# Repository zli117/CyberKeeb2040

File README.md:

# CyberKeeb 2040
A mechnical keyboard and a cyberdeck. Powered by [PicoMK](https://github.com/zli117/PicoMK) for communication between RP2040 and Pi Zero. Watch the demo on YouTube 👇.

# Table of Contents

- [CyberKeeb 2040](#cyberkeeb-2040)
- [Table of Contents](#table-of-contents)
- [Build](#build)
  - [PCB](#pcb)
  - [Frame](#frame)
- [Photos](#photos)
  - [V2](#v2)
  - [V1](#v1)
- [Q\&A](#qa)
- [PCB Library Licenses](#pcb-library-licenses)

# Build

[**V2 parts list and build instructions**](Docs/BuildInstructions_V2.md)

[V1 parts list and build instructions](Docs/BuildInstructions_V1.md)

## PCB
Everything is in [PCB/MainBoard](PCB/MainBoard) dir. Designed with Kicad 7.0. Make sure `Perfect DOS VGA 437 Font` is intalled on Windows, or if you use Arch, install the [ttf-perfectdos](https://aur.archlinux.org/packages/ttf-perfectdos) package. [PCB/MainBoard/Gerber](PCB/MainBoard/Gerber) dir contains the Gerber files for three fab houses: [JLCPCB](PCB/MainBoard/Gerber/JLCPCB/), [PCBWay](PCB/MainBoard/Gerber/PCBWay/), and [OSHPark](PCB/MainBoard/Gerber/OSHPark/). For JLCPCB and PCBWay, **make sure to select the Castellated Holes option** (this will increase the price, but I found it necessary for good castellated holes).

## Frame
The frame has three acrylic plates and is held together with screws and standoffs.

 * [Frame/MainBoard/TopBar.dxf](Frame/MainBoard/TopBar.dxf): 3mm acrlyic
 * [Frame/MainBoard/Plate.dxf](Frame/MainBoard/Plate.dxf): 1.5mm acrlyic
 * [Frame/MainBoard/Bottom.dxf](Frame/MainBoard/Bottom.dxf): 3mm acrlyic

# Photos

## V2

## V1

# Q&A

Special thanks to [icon-oclast](https://github.com/icon-oclast) for [asking](https://github.com/zli117/CyberKeeb2040/issues/2) these great questions.

> What are the dip switches used for? Is there a recommended default setting for these?

The 4 positions are for each line of the SPI connection between the pi pico and pi zero. This allows cutting the connections between pi pico and pi zero without cutting the power connections. I initially designed it for the (paranoid) scenario where I can't kill the pi zero, but doesn't want it to do autotype or receiving the key strokes, but I found such scenario increasing unlikely. So, if you don't want to solder the DIP switches, feel free to just short the corresponding pins.

> Presumably the switch/jumper labeled "pi power" controls pass-through power from the Pico to the Zero?

Yes.

> Is there a minimum USB current needed when powering both boards

I don't have the empirical measurements, but here's the estimate:
Pico: <20mA. Data source: https://mjoldfield.com/atelier/2021/11/pico-power.html
SSD1306: <7mA. Data source: https://hsel.co.uk/2018/12/04/ssd1306-power-consumption/
Pi Zero W: <400mA under stress. Data source: https://www.tomshardware.com/reviews/raspberry-pi-zero-2-w-review
Pi Zero 2 W: <600mA under stress.

So let's say it's 700mA if you want to stress the pi zero. I did run the stressberry on pi zero 2 w, with the display hat, and a wireless mouse receiver. The board is connected to the USB3.0 port and there's no under voltage warning, and no visible heat up on the cable or the connectors. However, due to differences on the motherboards, YMMY. I currently don't have a USB power meter to measure the actual current drawn.

> Is there a maximum safe current to pass-through (when using the optional display hat for example)?

The trace between pico and pi zero has width of 1mm, and length around 300mm. Assuming you're using 1oz copper thickness, it should result in a maximum current of 1.2 A for temperature rise of 10 degree C.

> Is it safe to power the zero independently by setting the pi power switch/jumper to off?

Yes.

> What about the two connectors at the bottom of the board, either 4-pin jst sockets as in the build instructions, or possibly 5-pin headers on some revisions of the pcb, how are they intended to be used?

They are for my future plans :) Essentially, they expose three buttons from the key scan matrix, and pin 26 and 27. Pin 26 and 27 are analog input pins and I2C 1. I'm planning to create a plugin module for the joystick mouse pad similar to the one I have on the Pico-Keyboard, and an I2C expansion board for more modules like a num pad. 

> What cool things can we do if we include the optional 90 degree pin header(s)?

The pin header under the small screen has been removed, because I figured it'll be difficult to use it for anything without creating a giant mess in the firmware. The other header exposes the addressable LEDs. Only WS2812 is supported and tested because it's used in the Pico-Keyboard. However, you might be able to use for other things as it's essentially a GPIO pin with ground and 5V, and a 330 ohm resister on the GPIO pin.

# PCB Library Licenses

 * Pico symbol, footprint from https://github.com/ncarandini/KiCad-RP-Pico under CC-BY-SA 4.0. 3D model for Pico is obtained from Raspberry Pi Foundation.
 * Pi Zero symbol, footprint and 3D model are from [SnapEDA](https://www.snapeda.com/parts/ADA3708/Adafruit%20Industries%20LLC/view-part/) under [CC BY-SA 4.0](https://support.snapeda.com/en/articles/2957814-what-is-the-license-for-symbols-and-footprints)
 * Key switch footprints and 3D models are from https://github.com/kiswitch/kiswitch
 * PJ320A symbol, footprint are from [Keebio-Parts.pretty](https://github.com/keebio/Keebio-Parts.pretty/blob/master/TRRS-PJ-320A.kicad_mod) under MIT License.
 * Other symbols are from KiCad library which is under CC-BY-SA 4.0 license. 

This work is licensed under a
[Creative Commons Attribution-ShareAlike 4.0 International License][cc-by-sa].

[![CC BY-SA 4.0][cc-by-sa-image]][cc-by-sa]

[cc-by-sa]: http://creativecommons.org/licenses/by-sa/4.0/
[cc-by-sa-image]: https://licensebuttons.net/l/by-sa/4.0/88x31.png
[cc-by-sa-shield]: https://img.shields.io/badge/License-CC%20BY--SA%204.0-lightgrey.svg

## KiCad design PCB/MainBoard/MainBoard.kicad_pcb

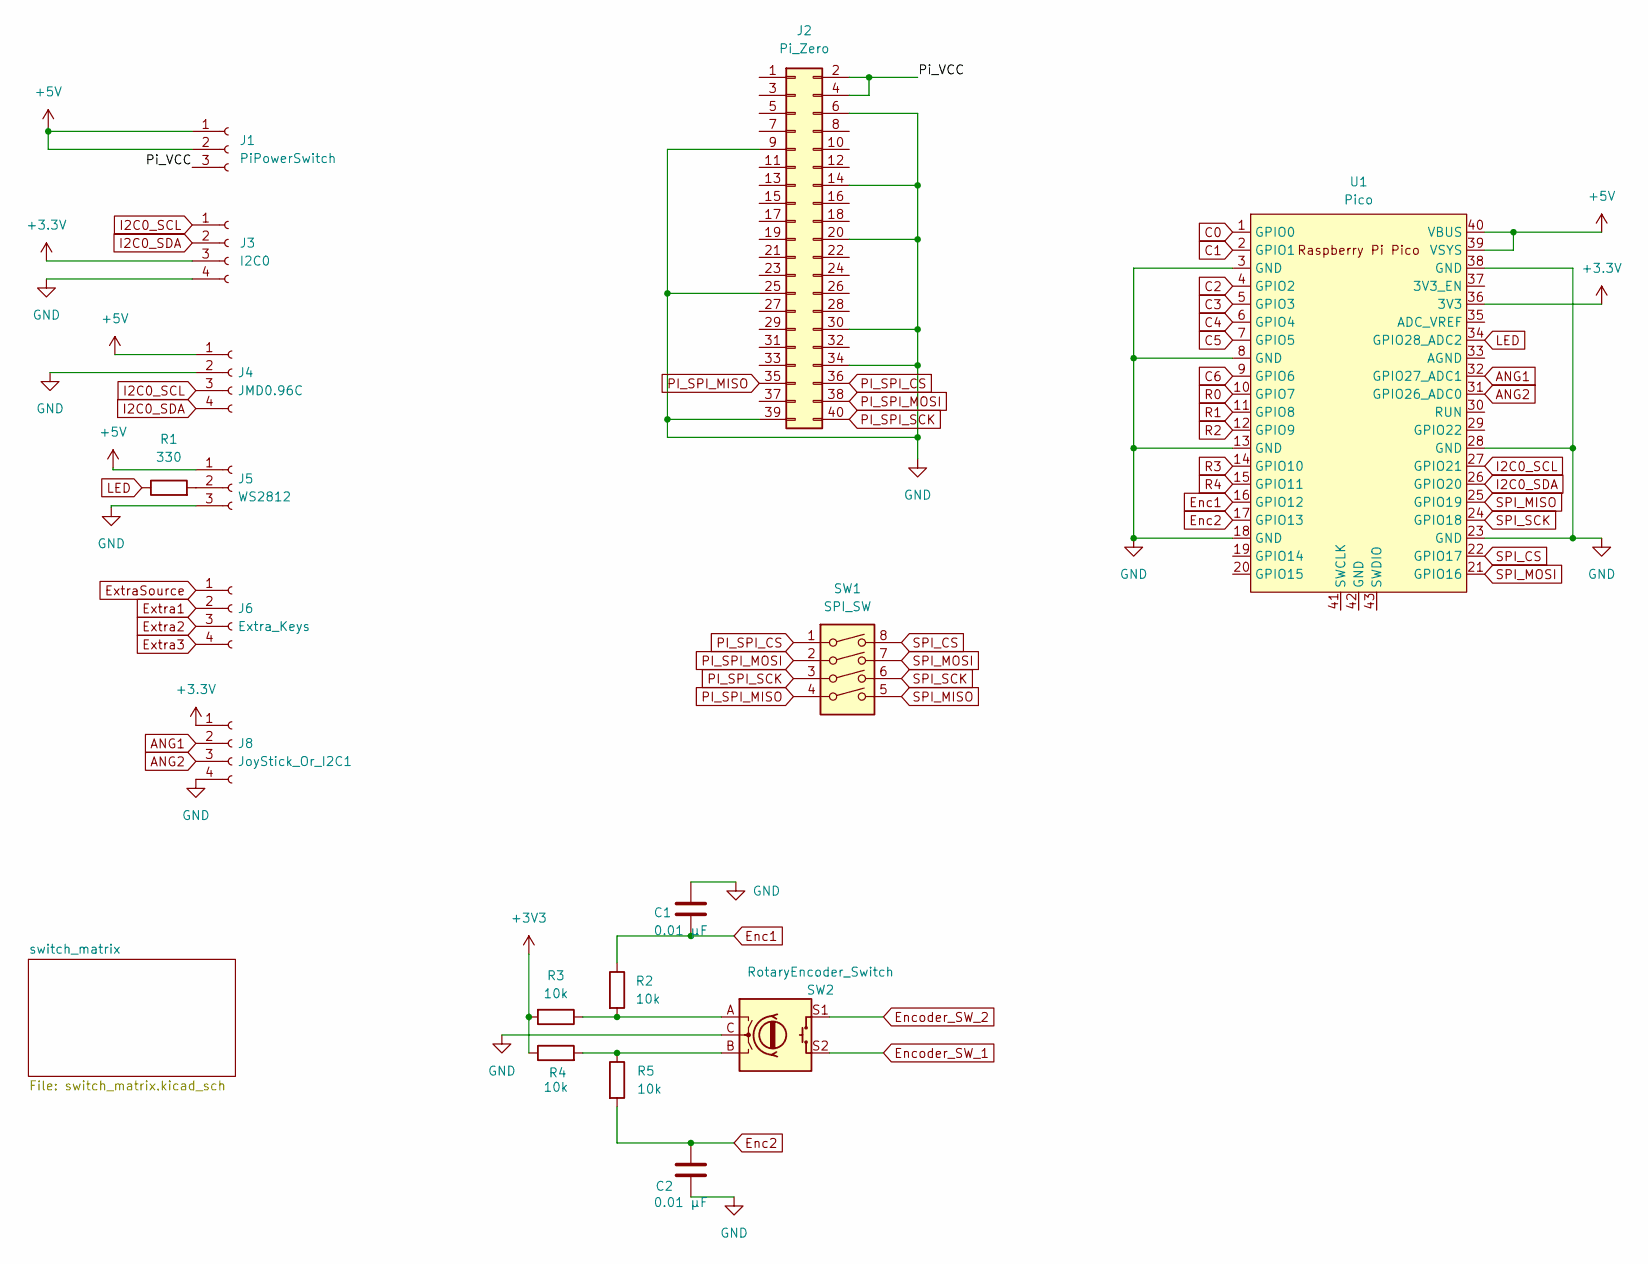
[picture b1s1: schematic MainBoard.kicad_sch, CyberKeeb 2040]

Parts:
C1, C2: 0.01 μF; C_1206_3216Metric_Pad1.33x1.80mm_HandSolder
J1: PiPowerSwitch; PinHeader_1x03_P2.54mm_Vertical
J2: Pi_Zero; Raspberry_Pi_Zero_Socketed_THT_MountingHoles_Castellated
J3: I2C0; PinHeader_1x04_P2.54mm_Horizontal
J4: JMD0.96C
J5: WS2812; PinHeader_1x03_P2.54mm_Horizontal
J6: Extra_Keys; JST_PH_S4B-PH-K_1x04_P2.00mm_Horizontal
J8: JoyStick_Or_I2C1; JST_PH_S4B-PH-K_1x04_P2.00mm_Horizontal
R1: 330; R_Axial_DIN0207_L6.3mm_D2.5mm_P10.16mm_Horizontal
R2, R3, R4, R5: 10k; R_Axial_DIN0207_L6.3mm_D2.5mm_P10.16mm_Horizontal
SW1: SPI_SW; SW_DIP_SPSTx04_Slide_6.7x11.72mm_W7.62mm_P2.54mm_LowProfile
SW2: RotaryEncoder_Switch; RotaryEncoder_Alps_EC11E-Switch_Vertical_H20mm_CircularMoun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
U1: Pico; RPi_Pico_SMD_TH

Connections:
+5V: J1.1, J1.2, J4.1, J5.1, U1.39 (VSYS), U1.40 (VBUS)
/Pi_VCC: J1.3, J2.2, J2.4
ANG1: J8.2, U1.32 (GPIO27_ADC1)
ANG2: J8.3, U1.31 (GPIO26_ADC0)
C0: U1.1 (GPIO0); also elsewhere on the board
C1: U1.2 (GPIO1); also elsewhere on the board
C2: U1.4 (GPIO2); also elsewhere on the board
C3: U1.5 (GPIO3); also elsewhere on the board
C4: U1.6 (GPIO4); also elsewhere on the board
C5: U1.7 (GPIO5); also elsewhere on the board
C6: U1.9 (GPIO6); also elsewhere on the board
Enc1: C1.2, R2.1, U1.16 (GPIO12)
Enc2: C2.1, R5.2, U1.17 (GPIO13)
Encoder_SW_1: SW2.S2; also elsewhere on the board
Encoder_SW_2: SW2.S1; also elsewhere on the board
Extra1: J6.2; also elsewhere on the board
Extra2: J6.3; also elsewhere on the board
Extra3: J6.4; also elsewhere on the board
ExtraSource: J6.1; also elsewhere on the board
GND: C1.1, C2.2, J2.6, J2.9, J2.14, J2.20, J2.25, J2.30, J2.34, J2.39, J3.4, J4.2, J5.3, J8.4, SW2.C, U1.3 (GND), U1.8 (GND), U1.13 (GND), U1.18 (GND), U1.23 (GND), U1.28 (GND), U1.38 (GND)
I2C0_SCL: J3.1, J4.3, U1.27 (GPIO21)
I2C0_SDA: J3.2, J4.4, U1.26 (GPIO20)
LED: R1.1, U1.34 (GPIO28_ADC2)
unnamed: J5.2, R1.2
unnamed: R2.2, R3.1, SW2.A
unnamed: R4.2, R5.1, SW2.B
PI_SPI_CS: J2.36, SW1.1
PI_SPI_MISO: J2.35, SW1.4
PI_SPI_MOSI: J2.38, SW1.2
PI_SPI_SCK: J2.40, SW1.3
R0: U1.10 (GPIO7); also elsewhere on the board
R1: U1.11 (GPIO8); also elsewhere on the board
R2: U1.12 (GPIO9); also elsewhere on the board
R3: U1.14 (GPIO10); also elsewhere on the board
R4: U1.15 (GPIO11); also elsewhere on the board
SPI_CS: SW1.8, U1.22 (GPIO17)
SPI_MISO: SW1.5, U1.25 (GPIO19)
SPI_MOSI: SW1.7, U1.21 (GPIO16)
SPI_SCK: SW1.6, U1.24 (GPIO18)

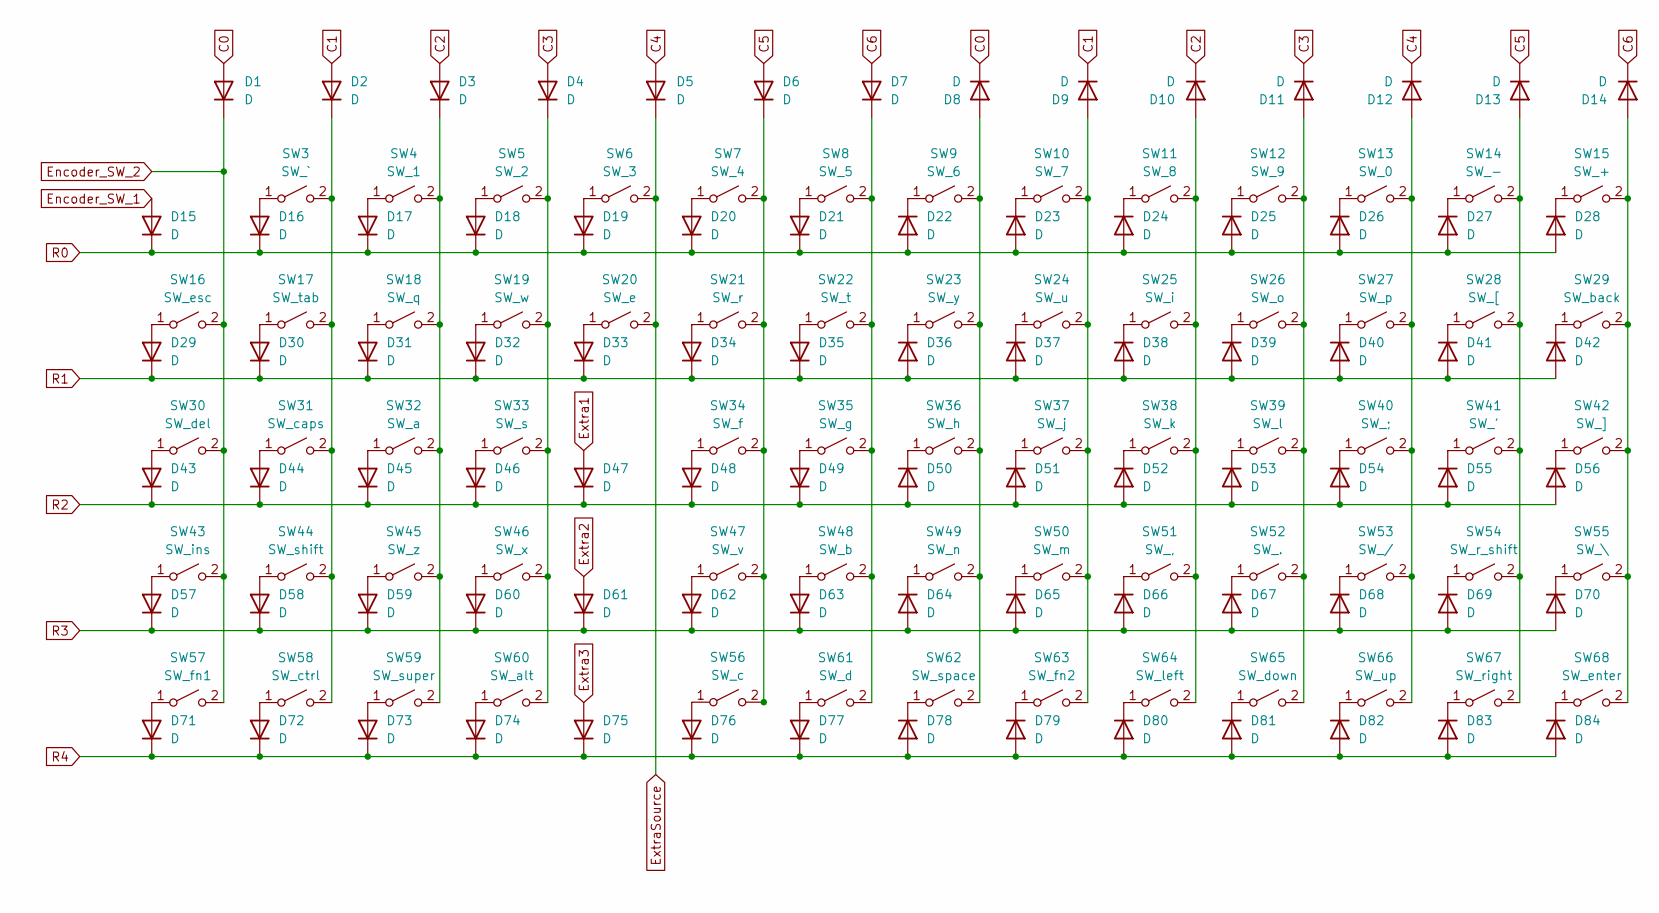
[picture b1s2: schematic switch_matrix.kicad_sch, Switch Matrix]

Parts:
D1, D2, D3, D4, D5, D6, D7, D8, D9, D10, D11, D12, D13, D14, D15, D16, D17, D18, D19, D20, D21, D22, D23, D24, D25, D26, D27, D28, D29, D30, D31, D32, D33, D34, D35, D36, D37, D38, D39, D40, D41, D42, D43, D44, D45, D46, D47, D48, D49, D50, D51, D52, D53, D54, D55, D56, D57, D58, D59, D60, D61, D62, D63, D64, D65, D66, D67, D68, D69, D70, D71, D72, D73, D74, D75, D76, D77, D78, D79, D80, D81, D82, D83, D84: D; D_DO-35_SOD27_P7.62mm_Horizontal
SW3: SW_`; SW_Hotswap_Kailh_MX_1.00u
SW4: SW_1; SW_Hotswap_Kailh_MX_1.00u
SW5: SW_2; SW_Hotswap_Kailh_MX_1.00u
SW6: SW_3; SW_Hotswap_Kailh_MX_1.00u
SW7: SW_4; SW_Hotswap_Kailh_MX_1.00u
SW8: SW_5; SW_Hotswap_Kailh_MX_1.00u
SW9: SW_6; SW_Hotswap_Kailh_MX_1.00u
SW10: SW_7; SW_Hotswap_Kailh_MX_1.00u
SW11: SW_8; SW_Hotswap_Kailh_MX_1.00u
SW12: SW_9; SW_Hotswap_Kailh_MX_1.00u
SW13: SW_0; SW_Hotswap_Kailh_MX_1.00u
SW14: SW_-; SW_Hotswap_Kailh_MX_1.00u
SW15: SW_+; SW_Hotswap_Kailh_MX_1.00u
SW16: SW_esc; SW_Hotswap_Kailh_MX_1.00u
SW17: SW_tab; SW_Hotswap_Kailh_MX_1.50u
SW18: SW_q; SW_Hotswap_Kailh_MX_1.00u
SW19: SW_w; SW_Hotswap_Kailh_MX_1.00u
SW20: SW_e; SW_Hotswap_Kailh_MX_1.00u
SW21: SW_r; SW_Hotswap_Kailh_MX_1.00u
SW22: SW_t; SW_Hotswap_Kailh_MX_1.00u
SW23: SW_y; SW_Hotswap_Kailh_MX_1.00u
SW24: SW_u; SW_Hotswap_Kailh_MX_1.00u
SW25: SW_i; SW_Hotswap_Kailh_MX_1.00u
SW26: SW_o; SW_Hotswap_Kailh_MX_1.00u
SW27: SW_p; SW_Hotswap_Kailh_MX_1.00u
SW28: SW_[; SW_Hotswap_Kailh_MX_1.00u
SW29: SW_back; SW_Hotswap_Kailh_MX_2.00u
SW30: SW_del; SW_Hotswap_Kailh_MX_1.00u
SW31: SW_caps; SW_Hotswap_Kailh_MX_1.75u
SW32: SW_a; SW_Hotswap_Kailh_MX_1.00u
SW33: SW_s; SW_Hotswap_Kailh_MX_1.00u
SW34: SW_f; SW_Hotswap_Kailh_MX_1.00u
SW35: SW_g; SW_Hotswap_Kailh_MX_1.00u
SW36: SW_h; SW_Hotswap_Kailh_MX_1.00u
SW37: SW_j; SW_Hotswap_Kailh_MX_1.00u
SW38: SW_k; SW_Hotswap_Kailh_MX_1.00u
SW39: SW_l; SW_Hotswap_Kailh_MX_1.00u
SW40: SW_;; SW_Hotswap_Kailh_MX_1.00u
SW41: SW_'; SW_Hotswap_Kailh_MX_1.00u
SW42: SW_]; SW_Hotswap_Kailh_MX_1.00u
SW43: SW_ins; SW_Hotswap_Kailh_MX_1.00u
SW44: SW_shift; SW_Hotswap_Kailh_MX_2.25u
SW45: SW_z; SW_Hotswap_Kailh_MX_1.00u
SW46: SW_x; SW_Hotswap_Kailh_MX_1.00u
SW47: SW_v; SW_Hotswap_Kailh_MX_1.00u
SW48: SW_b; SW_Hotswap_Kailh_MX_1.00u
SW49: SW_n; SW_Hotswap_Kailh_MX_1.00u
SW50: SW_m; SW_Hotswap_Kailh_MX_1.00u
SW51: SW_,; SW_Hotswap_Kailh_MX_1.00u
SW52: SW_.; SW_Hotswap_Kailh_MX_1.00u
SW53: SW_/; SW_Hotswap_Kailh_MX_1.00u
SW54: SW_r_shift; SW_Hotswap_Kailh_MX_2.75u
SW55: SW_\; SW_Hotswap_Kailh_MX_1.50u
SW56: SW_c; SW_Hotswap_Kailh_MX_1.00u
SW57: SW_fn1; SW_Hotswap_Kailh_MX_1.00u
SW58: SW_ctrl; SW_Hotswap_Kailh_MX_1.25u
SW59: SW_super; SW_Hotswap_Kailh_MX_1.25u
SW60: SW_alt; SW_Hotswap_Kailh_MX_1.25u
SW61: SW_d; SW_Hotswap_Kailh_MX_1.00u
SW62: SW_space; SW_Hotswap_Kailh_MX_6.25u
SW63: SW_fn2; SW_Hotswap_Kailh_MX_1.00u
SW64: SW_left; SW_Hotswap_Kailh_MX_1.00u
SW65: SW_down; SW_Hotswap_Kailh_MX_1.00u
SW66: SW_up; SW_Hotswap_Kailh_MX_1.00u
SW67: SW_right; SW_Hotswap_Kailh_MX_1.00u
SW68: SW_enter; SW_Hotswap_Kailh_MX_2.25u

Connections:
C0: D1.2 (A), D8.1 (K); also elsewhere on the board
C1: D2.2 (A), D9.1 (K); also elsewhere on the board
C2: D3.2 (A), D10.1 (K); also elsewhere on the board
C3: D4.2 (A), D11.1 (K); also elsewhere on the board
C4: D5.2 (A), D12.1 (K); also elsewhere on the board
C5: D6.2 (A), D13.1 (K); also elsewhere on the board
C6: D7.2 (A), D14.1 (K); also elsewhere on the board
Encoder_SW_1: D15.2 (A); also elsewhere on the board
Encoder_SW_2: D1.1 (K), SW16.2 (B), SW30.2 (B), SW43.2 (B), SW57.2 (B); also elsewhere on the board
Extra1: D47.2 (A); also elsewhere on the board
Extra2: D61.2 (A); also elsewhere on the board
Extra3: D75.2 (A); also elsewhere on the board
ExtraSource: D5.1 (K), SW6.2 (B), SW20.2 (B); also elsewhere on the board
unnamed: D2.1 (K), SW3.2 (B), SW17.2 (B), SW31.2 (B), SW44.2 (B), SW58.2 (B)
unnamed: D3.1 (K), SW4.2 (B), SW18.2 (B), SW32.2 (B), SW45.2 (B), SW59.2 (B)
unnamed: D4.1 (K), SW5.2 (B), SW19.2 (B), SW33.2 (B), SW46.2 (B), SW60.2 (B)
unnamed: D6.1 (K), SW7.2 (B), SW21.2 (B), SW34.2 (B), SW47.2 (B), SW56.2 (B)
unnamed: D7.1 (K), SW8.2 (B), SW22.2 (B), SW35.2 (B), SW48.2 (B), SW61.2 (B)
unnamed: D8.2 (A), SW9.2 (B), SW23.2 (B), SW36.2 (B), SW49.2 (B), SW62.2 (B)
unnamed: D9.2 (A), SW10.2 (B), SW24.2 (B), SW37.2 (B), SW50.2 (B), SW63.2 (B)
unnamed: D10.2 (A), SW11.2 (B), SW25.2 (B), SW38.2 (B), SW51.2 (B), SW64.2 (B)
unnamed: D11.2 (A), SW12.2 (B), SW26.2 (B), SW39.2 (B), SW52.2 (B), SW65.2 (B)
unnamed: D12.2 (A), SW13.2 (B), SW27.2 (B), SW40.2 (B), SW53.2 (B), SW66.2 (B)
unnamed: D13.2 (A), SW14.2 (B), SW28.2 (B), SW41.2 (B), SW54.2 (B), SW67.2 (B)
unnamed: D14.2 (A), SW15.2 (B), SW29.2 (B), SW42.2 (B), SW55.2 (B), SW68.2 (B)
unnamed: D16.2 (A), SW3.1 (A)
unnamed: D17.2 (A), SW4.1 (A)
unnamed: D18.2 (A), SW5.1 (A)
unnamed: D19.2 (A), SW6.1 (A)
unnamed: D20.2 (A), SW7.1 (A)
unnamed: D21.2 (A), SW8.1 (A)
unnamed: D22.1 (K), SW9.1 (A)
unnamed: D23.1 (K), SW10.1 (A)
unnamed: D24.1 (K), SW11.1 (A)
unnamed: D25.1 (K), SW12.1 (A)
unnamed: D26.1 (K), SW13.1 (A)
unnamed: D27.1 (K), SW14.1 (A)
unnamed: D28.1 (K), SW15.1 (A)
unnamed: D29.2 (A), SW16.1 (A)
unnamed: D30.2 (A), SW17.1 (A)
unnamed: D31.2 (A), SW18.1 (A)
unnamed: D32.2 (A), SW19.1 (A)
unnamed: D33.2 (A), SW20.1 (A)
unnamed: D34.2 (A), SW21.1 (A)
unnamed: D35.2 (A), SW22.1 (A)
unnamed: D36.1 (K), SW23.1 (A)
unnamed: D37.1 (K), SW24.1 (A)
unnamed: D38.1 (K), SW25.1 (A)
unnamed: D39.1 (K), SW26.1 (A)
unnamed: D40.1 (K), SW27.1 (A)
unnamed: D41.1 (K), SW28.1 (A)
unnamed: D42.1 (K), SW29.1 (A)
unnamed: D43.2 (A), SW30.1 (A)
unnamed: D44.2 (A), SW31.1 (A)
unnamed: D45.2 (A), SW32.1 (A)
unnamed: D46.2 (A), SW33.1 (A)
unnamed: D48.2 (A), SW34.1 (A)
unnamed: D49.2 (A), SW35.1 (A)
unnamed: D50.1 (K), SW36.1 (A)
unnamed: D51.1 (K), SW37.1 (A)
unnamed: D52.1 (K), SW38.1 (A)
unnamed: D53.1 (K), SW39.1 (A)
unnamed: D54.1 (K), SW40.1 (A)
unnamed: D55.1 (K), SW41.1 (A)
unnamed: D56.1 (K), SW42.1 (A)
unnamed: D57.2 (A), SW43.1 (A)
unnamed: D58.2 (A), SW44.1 (A)
unnamed: D59.2 (A), SW45.1 (A)
unnamed: D60.2 (A), SW46.1 (A)
unnamed: D62.2 (A), SW47.1 (A)
unnamed: D63.2 (A), SW48.1 (A)
unnamed: D64.1 (K), SW49.1 (A)
unnamed: D65.1 (K), SW50.1 (A)
unnamed: D66.1 (K), SW51.1 (A)
unnamed: D67.1 (K), SW52.1 (A)
unnamed: D68.1 (K), SW53.1 (A)
unnamed: D69.1 (K), SW54.1 (A)
unnamed: D70.1 (K), SW55.1 (A)
unnamed: D71.2 (A), SW57.1 (A)
unnamed: D72.2 (A), SW58.1 (A)
unnamed: D73.2 (A), SW59.1 (A)
unnamed: D74.2 (A), SW60.1 (A)
unnamed: D77.2 (A), SW61.1 (A)
unnamed: D78.1 (K), SW62.1 (A)
unnamed: D79.1 (K), SW63.1 (A)
unnamed: D80.1 (K), SW64.1 (A)
unnamed: D81.1 (K), SW65.1 (A)
unnamed: D82.1 (K), SW66.1 (A)
unnamed: D83.1 (K), SW67.1 (A)
unnamed: D84.1 (K), SW68.1 (A)
R0: D15.1 (K), D16.1 (K), D17.1 (K), D18.1 (K), D19.1 (K), D20.1 (K), D21.1 (K), D22.2 (A), D23.2 (A), D24.2 (A), D25.2 (A), D26.2 (A), D27.2 (A), D28.2 (A); also elsewhere on the board
R1: D29.1 (K), D30.1 (K), D31.1 (K), D32.1 (K), D33.1 (K), D34.1 (K), D35.1 (K), D36.2 (A), D37.2 (A), D38.2 (A), D39.2 (A), D40.2 (A), D41.2 (A), D42.2 (A); also elsewhere on the board
R2: D43.1 (K), D44.1 (K), D45.1 (K), D46.1 (K), D47.1 (K), D48.1 (K), D49.1 (K), D50.2 (A), D51.2 (A), D52.2 (A), D53.2 (A), D54.2 (A), D55.2 (A), D56.2 (A); also elsewhere on the board
R3: D57.1 (K), D58.1 (K), D59.1 (K), D60.1 (K), D61.1 (K), D62.1 (K), D63.1 (K), D64.2 (A), D65.2 (A), D66.2 (A), D67.2 (A), D68.2 (A), D69.2 (A), D70.2 (A); also elsewhere on the board
R4: D71.1 (K), D72.1 (K), D73.1 (K), D74.1 (K), D75.1 (K), D76.1 (K), D77.1 (K), D78.2 (A), D79.2 (A), D80.2 (A), D81.2 (A), D82.2 (A), D83.2 (A), D84.2 (A); also elsewhere on the board

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
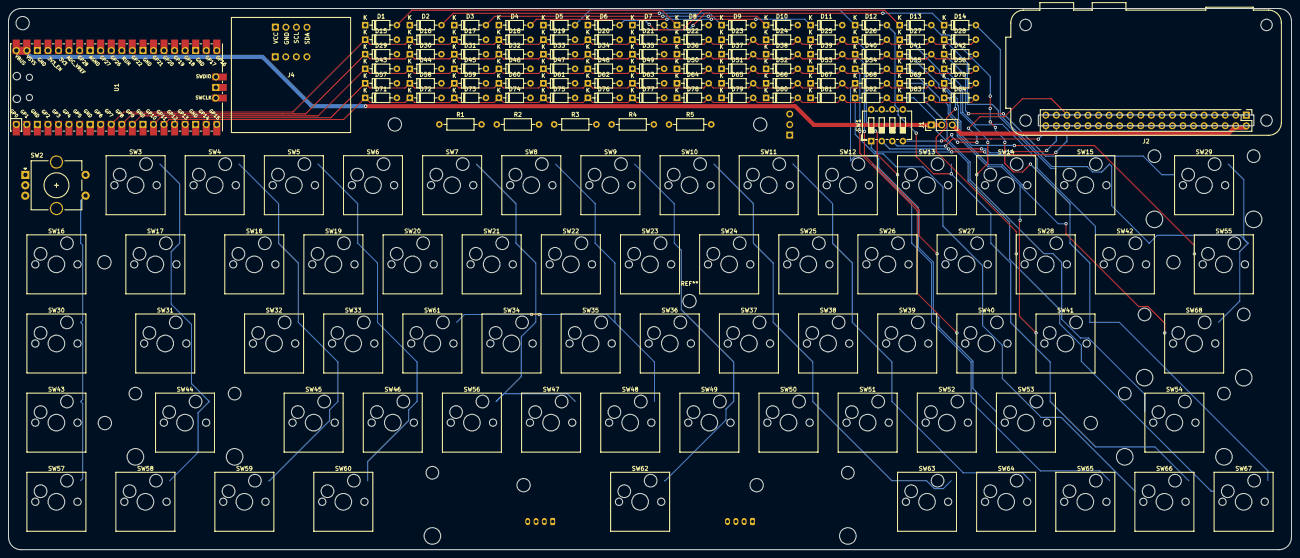
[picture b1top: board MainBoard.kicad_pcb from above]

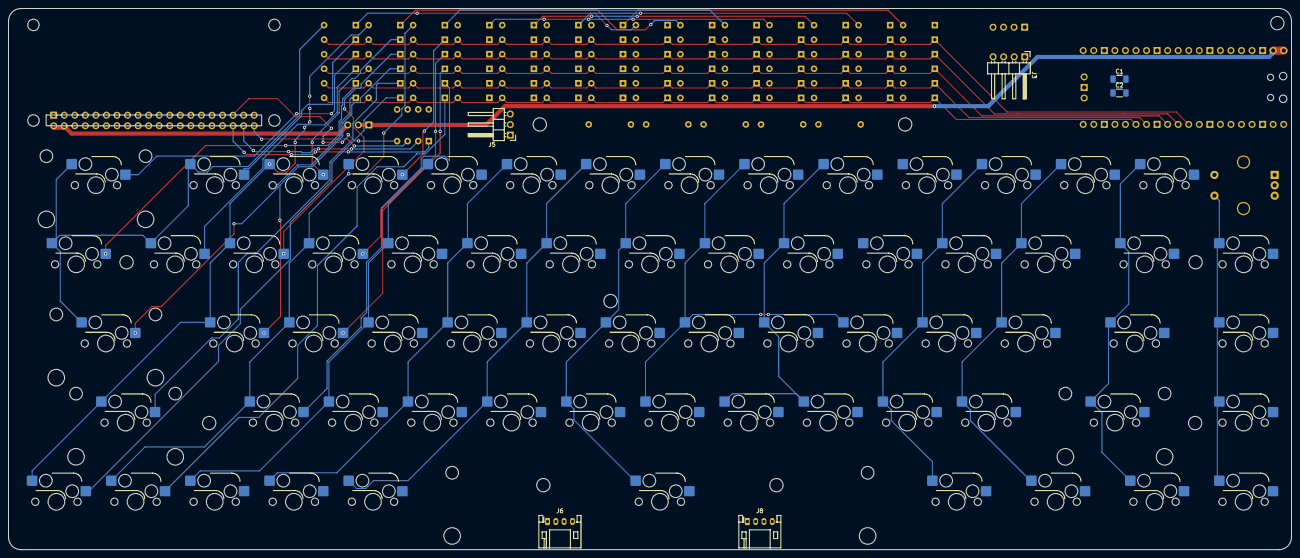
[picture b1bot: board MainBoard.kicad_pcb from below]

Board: 2 copper layers, 308.8 x 130.2 mm, 167 parts (6 on the bottom side), 117 nets.

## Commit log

2023-06-10 Added diodes for the duplex layout
2023-06-11 Updated 3d model
2023-06-11 Tentative layout
2023-06-11 Layout settled
2023-06-11 Updated layout to add mounting holes
2023-06-11 Crazy wiring
2023-06-12 Whatever
2023-06-14 Updated PCB
2023-06-14 Added gerber
2023-06-15 Added silkscreen label
2023-06-15 Updated github url
2023-06-18 Updated pcb a bit
2023-06-18 Custom diode footprint with proper silkscreen
2023-06-18 Fixed solder mask around the mounting hole for pi
2023-06-23 Added pcb step file
2023-06-24 Fixed 3d model for pi zero
2023-07-02 Updated 3d model for zero
2023-07-02 Added frame stl and dxf files
2023-07-03 Changed self tapping diameter
2023-07-03 Updated tapping hole diameter
2023-07-04 Fixed bottom plate hole
2023-07-08 Fixed the spacers, and added a thumb rest
2023-07-21 Updated bottom dxf
2023-08-19 Updated bottom spacer
2023-08-19 Updated plate dxf to have a rounded corner
2023-08-19 Use switch instead of jumper
2023-08-20 Added f3d file
2023-08-20 Create LICENSE
2023-08-20 Added instruction to install the driver
2023-08-20 Added table of contents
2023-09-04 Updated the bottom connector, and replotted the files
2023-09-04 Fixed pick and place center for switch footprint
2023-09-04 Forgot to uncomment something
2023-09-04 Fixed silkscreen for the diodes
2023-09-04 Added SMT pads to the diodes
2023-09-04 Fixed silkscreen
2023-09-04 Added 0402 SMT capacitor
2023-09-05 Regenerate gerber
2023-09-06 Cleaned up a bit
2023-09-06 Small update
2023-09-06 Changed the footprint and silkscreen
2023-09-09 Updated the diode silkscreen
2023-09-10 Updated the footprint of the pi zero
2023-09-13 Updated the bottom dxf
2023-09-13 Removed big step file
2023-09-21 Updated footprint
2023-09-21 Fixed trace being dangurously close to the border issue
2023-09-21 Freeze positions
2023-09-21 Updated gitignore
2023-09-23 Removed some large files. Updated the laser cutting designs
2023-09-24 Updated bottom plate
2023-09-24 Removed old files
2023-09-24 Updated name for a switch
2023-09-24 Minor changes
2023-09-25 Small update to the traces
2023-09-25 Another small update to the traces
2023-09-27 Refill the zones
2023-09-28 Updates to the screw size
2023-09-28 Updated a trace
2023-10-02 Moved traces further away from the edge
2023-10-07 Added gerber files
2023-10-09 Updated silkscreen
2023-10-12 Added dimensions
2023-10-13 Added copper cutout for the antenna
2023-11-19 Updated for v2
2023-11-19 Added frame assembly
2023-11-19 Updated images
